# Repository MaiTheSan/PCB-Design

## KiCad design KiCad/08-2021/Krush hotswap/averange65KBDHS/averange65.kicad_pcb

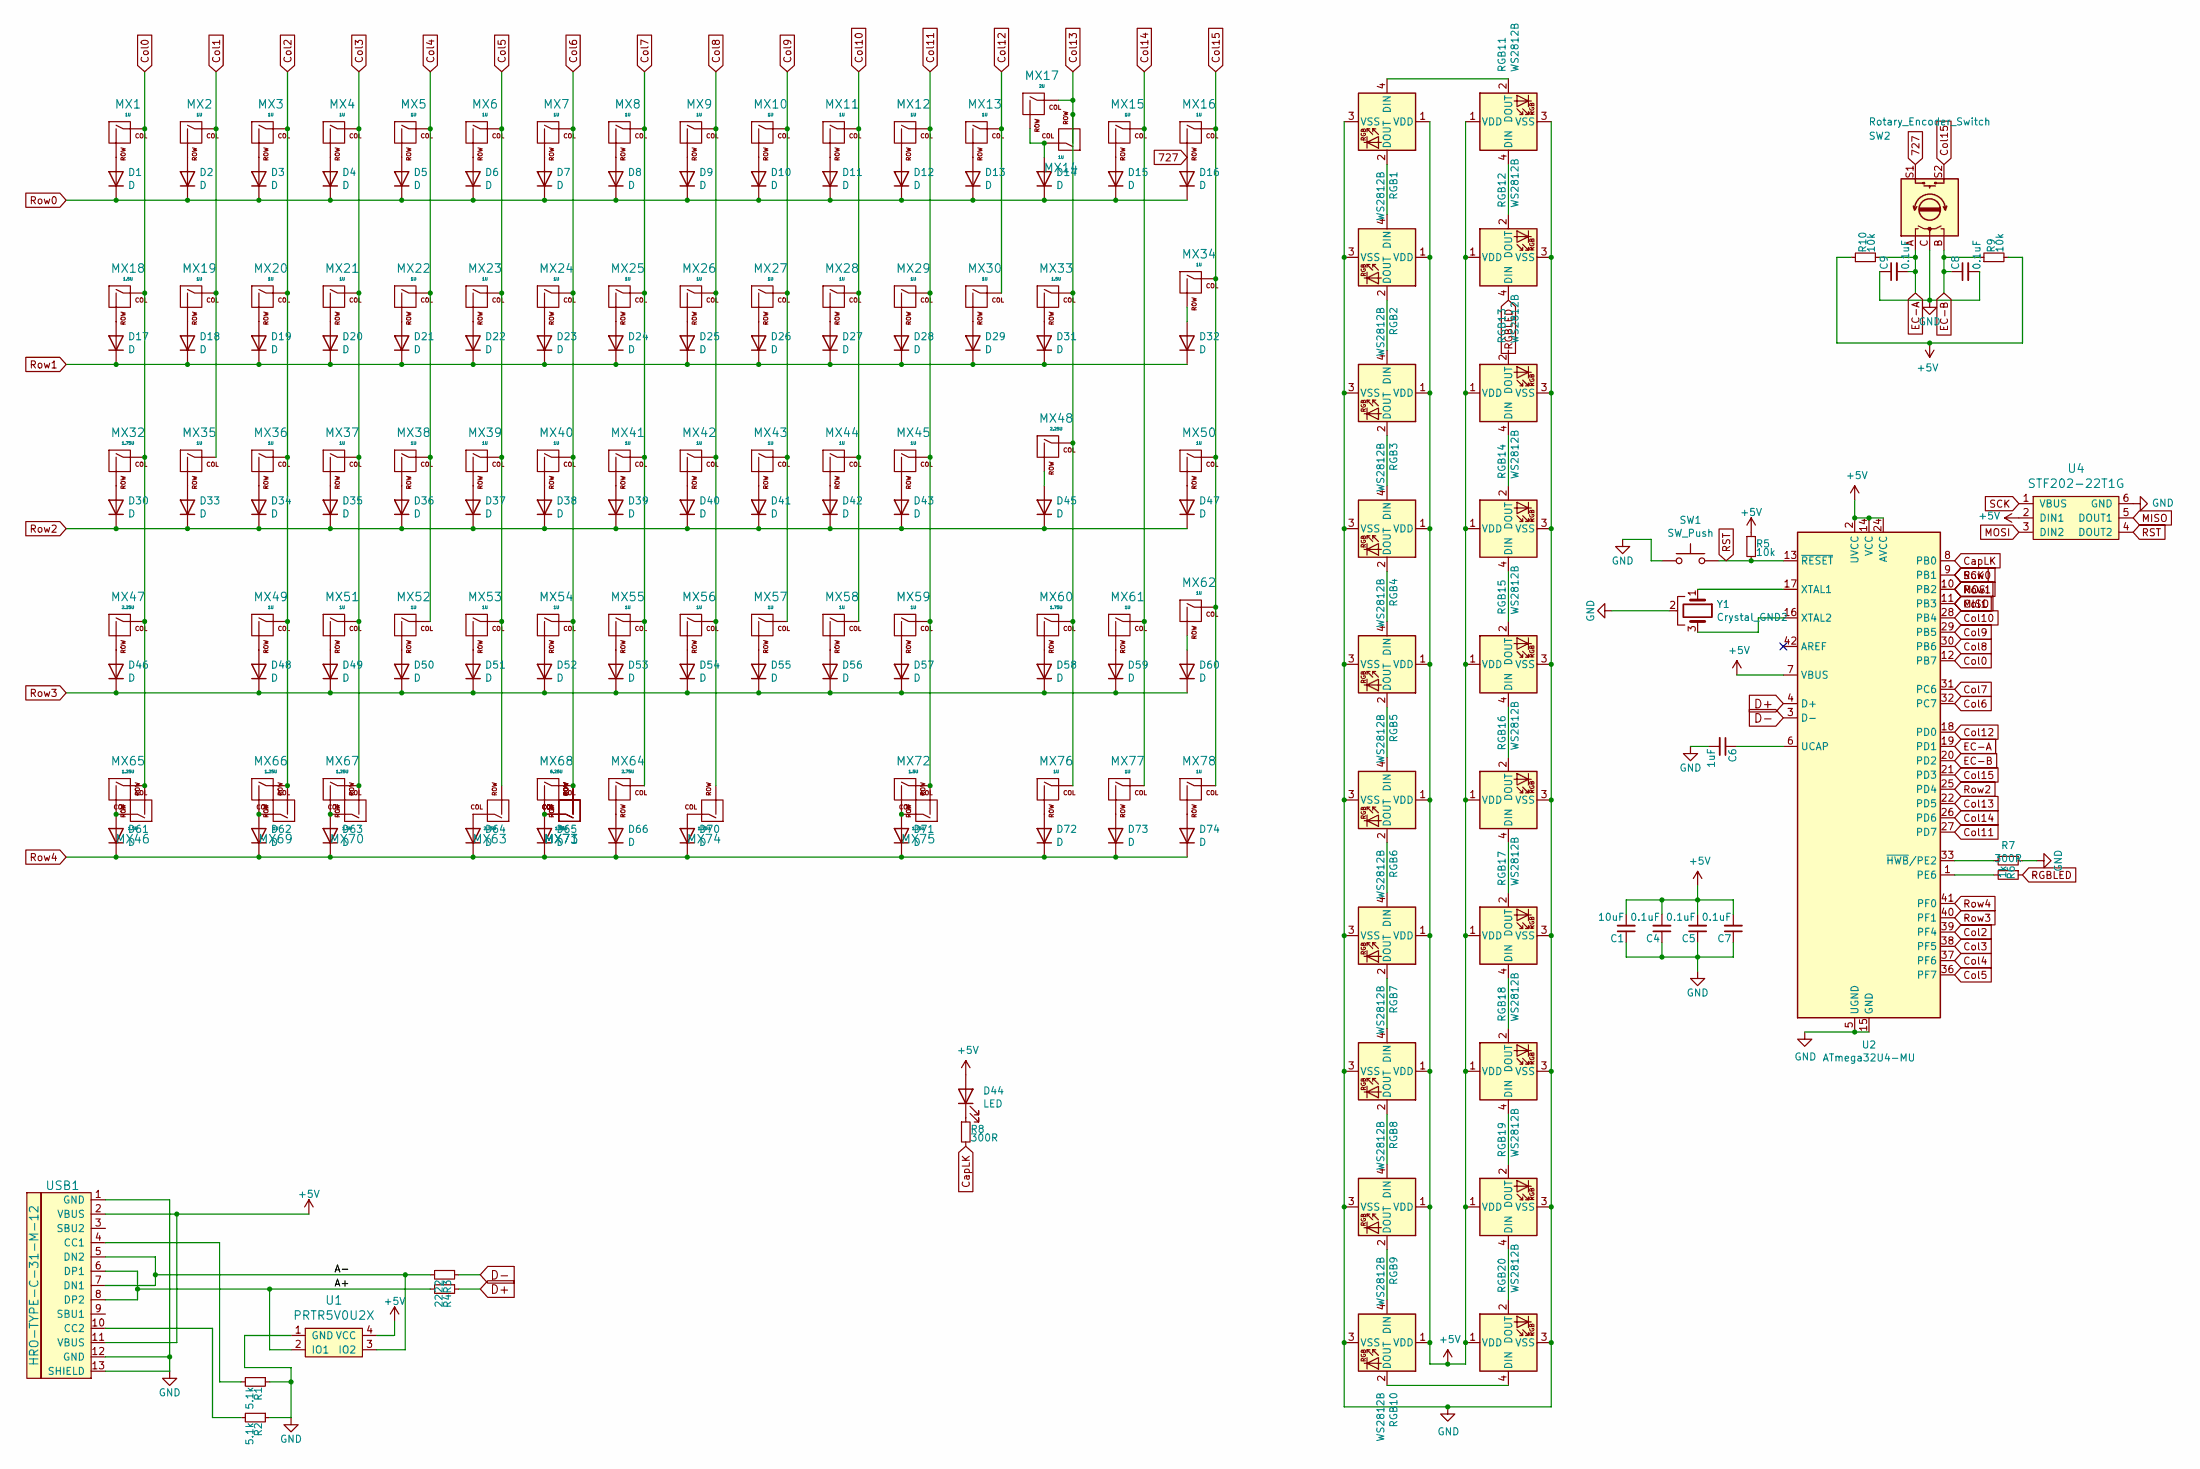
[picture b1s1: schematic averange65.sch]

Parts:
C1: 10uF; C_0603
C4, C5, C7, C8, C9: 0.1uF; C_0603
C6: 1uF; C_0603
D1, D2, D3, D4, D5, D6, D7, D8, D9, D10, D11, D12, D13, D14, D15, D16, D17, D18, D19, D20, D21, D22, D23, D24, D25, D26, D27, D28, D29, D30, D31, D32, D33, D34, D35, D36, D37, D38, D39, D40, D41, D42, D43, D45, D46, D47, D48, D49, D50, D51, D52, D53, D54, D55, D56, D57, D58, D59, D60, D61, D62, D63, D64, D65, D66, D70, D71, D72, D73, D74: D; DIODE_1206_SawnsProjects
D44: LED; LED-6028
MX1, MX2, MX3, MX4, MX5, MX6, MX7, MX8, MX9, MX10, MX11, MX12, MX13, MX14, MX15, MX16, MX19, MX20, MX21, MX22, MX23, MX24, MX25, MX26, MX27, MX28, MX29, MX30, MX34, MX35, MX36, MX37, MX38, MX39, MX40, MX41, MX42, MX43, MX44, MX45, MX49, MX50, MX51, MX52, MX53, MX54, MX55, MX56, MX57, MX58, MX59, MX61, MX62, MX69, MX76, MX77, MX78: 1U; MXOnly-1U-Hotswap
MX17: 2U; MXOnly-2U-Hotswap
MX18, MX33, MX46, MX70, MX72: 1.5U; MXOnly-1.5U-Hotswap
MX32, MX60: 1.75U; MXOnly-1.75U-Hotswap
MX47, MX48: 2.25U; MXOnly-2.25U-Hotswap
MX63: 2.25U; MXOnly-2.25U-Hotswap-ReversedStabilizers
MX64: 2.75U; MXOnly-2.75U-Hotswap-ReversedStabilizers
MX65, MX66, MX67, MX73, MX74, MX75: 1.25U; MXOnly-1.25U-Hotswap
MX68: 6.25U; MXOnly-6.25U-Hotswap
MX71: 7U; MXOnly-7U-Hotswap-ReversedStabilizers
R1, R2: 5.1k; R_0805
R3, R4: 22; R_0603
R5, R9, R10: 10k; R_0805
R6: 1k; R_0805
R7, R8: 300R; R_0805
RGB1, RGB2, RGB3, RGB4, RGB5, RGB6, RGB7, RGB8, RGB9, RGB10, RGB11, RGB12, RGB13, RGB14, RGB15, RGB16, RGB17, RGB18, RGB19, RGB20: WS2812B; LED_WS2812B_PLCC4_5.0x5.0mm_P3.2mm
SW1: SW_Push; SKQG-1155865
SW2: Rotary_Encoder_Switch; RotaryEncoder_Alps_EC11E-Switch_Vertical_H20mm_Center
U1: PRTR5V0U2X; SOT143B
U2: ATmega32U4-MU; QFN-44-1EP_7x7mm_P0.5mm_EP5.15x5.15mm
U4: STF202-22T1G; Tag-Connect_TC2030-IDC-NL_2x03_P1.27mm_Vertical
USB1: HRO-TYPE-C-31-M-12; HRO-TYPE-C-31-M-12-Assembly
Y1: Crystal_GND2; Resonator_SMD_muRata_CSTxExxV-3Pin_3.0x1.1mm

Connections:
727: D16.2 (A), MX16.2 (ROW), SW2.S1
+5V: C1.2, C4.2, C5.2, C7.2, D44.2 (A), R5.1, R9.2, R10.1, RGB1.1 (VDD), RGB2.1 (VDD), RGB3.1 (VDD), RGB4.1 (VDD), RGB5.1 (VDD), RGB6.1 (VDD), RGB7.1 (VDD), RGB8.1 (VDD), RGB9.1 (VDD), RGB10.1 (VDD), RGB11.1 (VDD), RGB12.1 (VDD), RGB13.1 (VDD), RGB14.1 (VDD), RGB15.1 (VDD), RGB16.1 (VDD), RGB17.1 (VDD), RGB18.1 (VDD), RGB19.1 (VDD), RGB20.1 (VDD), U1.4 (VCC), U2.2 (UVCC), U2.7 (VBUS), U2.14 (VCC), U2.24 (AVCC), U2.34 (VCC), U2.44 (AVCC), U4.2 (DIN1), USB1.2 (VBUS), USB1.11 (VBUS)
/A+: R4.2, U1.2 (IO1), USB1.6 (DP1), USB1.8 (DP2)
/A-: R3.2, U1.3 (IO2), USB1.5 (DN2), USB1.7 (DN1)
CapLK: R8.2, U2.8 (PB0)
Col0: MX1.1 (COL), MX18.1 (COL), MX32.1 (COL), MX46.2 (ROW), MX47.1 (COL), MX65.1 (COL), U2.12 (PB7)
Col1: MX2.1 (COL), MX19.1 (COL), MX35.1 (COL), U2.11 (PB3), U4.5 (DOUT1)
Col2: MX3.1 (COL), MX20.1 (COL), MX36.1 (COL), MX49.1 (COL), MX66.1 (COL), MX69.2 (ROW), U2.39 (PF4)
Col3: MX4.1 (COL), MX21.1 (COL), MX37.1 (COL), MX51.1 (COL), MX67.1 (COL), MX70.2 (ROW), U2.38 (PF5)
Col4: MX5.1 (COL), MX22.1 (COL), MX38.1 (COL), MX52.1 (COL), U2.37 (PF6)
Col5: MX6.1 (COL), MX23.1 (COL), MX39.1 (COL), MX53.1 (COL), MX63.2 (ROW), U2.36 (PF7)
Col6: MX7.1 (COL), MX24.1 (COL), MX40.1 (COL), MX54.1 (COL), MX68.1 (COL), MX71.2 (ROW), MX73.2 (ROW), U2.32 (PC7)
Col7: MX8.1 (COL), MX25.1 (COL), MX41.1 (COL), MX55.1 (COL), MX64.1 (COL), U2.31 (PC6)
Col8: MX9.1 (COL), MX26.1 (COL), MX42.1 (COL), MX56.1 (COL), MX74.2 (ROW), U2.30 (PB6)
Col9: MX10.1 (COL), MX27.1 (COL), MX43.1 (COL), MX57.1 (COL), U2.29 (PB5)
Col10: MX11.1 (COL), MX28.1 (COL), MX44.1 (COL), MX58.1 (COL), U2.28 (PB4)
Col11: MX12.1 (COL), MX29.1 (COL), MX45.1 (COL), MX59.1 (COL), MX72.1 (COL), MX75.2 (ROW), U2.27 (PD7)
Col12: MX13.1 (COL), MX30.1 (COL), U2.18 (PD0)
Col13: MX14.2 (ROW), MX17.1 (COL), MX33.1 (COL), MX48.1 (COL), MX60.1 (COL), MX76.1 (COL), U2.22 (PD5)
Col14: MX15.1 (COL), MX61.1 (COL), MX77.1 (COL), U2.26 (PD6)
Col15: MX16.1 (COL), MX34.1 (COL), MX50.1 (COL), MX62.1 (COL), MX78.1 (COL), SW2.S2, U2.21 (PD3)
D+: R4.1, U2.4 (D+)
D-: R3.1, U2.3 (D-)
EC-A: C9.2, R10.2, SW2.A, U2.19 (PD1)
EC-B: C8.1, R9.1, SW2.B, U2.20 (PD2)
GND: C1.1, C4.1, C5.1, C6.2, C7.1, C8.2, C9.1, R1.1, R2.1, R6.1, RGB1.3 (VSS), RGB2.3 (VSS), RGB3.3 (VSS), RGB4.3 (VSS), RGB5.3 (VSS), RGB6.3 (VSS), RGB7.3 (VSS), RGB8.3 (VSS), RGB9.3 (VSS), RGB10.3 (VSS), RGB11.3 (VSS), RGB12.3 (VSS), RGB13.3 (VSS), RGB14.3 (VSS), RGB15.3 (VSS), RGB16.3 (VSS), RGB17.3 (VSS), RGB18.3 (VSS), RGB19.3 (VSS), RGB20.3 (VSS), SW1.1, SW2.C, U1.1 (GND), U2.5 (UGND), U2.15 (GND), U2.23 (GND), U2.35 (GND), U2.43 (GND), U2.45 (GND), U4.6 (GND), USB1.1 (GND), USB1.12 (GND), USB1.13 (SHIELD), Y1.2
MOSI: D17.1 (K), D18.1 (K), D19.1 (K), D20.1 (K), D21.1 (K), D22.1 (K), D23.1 (K), D24.1 (K), D25.1 (K), D26.1 (K), D27.1 (K), D28.1 (K), D29.1 (K), D31.1 (K), D32.1 (K), U2.10 (PB2), U4.3 (DIN2)
unnamed: C6.1, U2.6 (UCAP)
unnamed: D1.2 (A), MX1.2 (ROW)
unnamed: D2.2 (A), MX2.2 (ROW)
unnamed: D3.2 (A), MX3.2 (ROW)
unnamed: D4.2 (A), MX4.2 (ROW)
unnamed: D5.2 (A), MX5.2 (ROW)
unnamed: D6.2 (A), MX6.2 (ROW)
unnamed: D7.2 (A), MX7.2 (ROW)
unnamed: D8.2 (A), MX8.2 (ROW)
unnamed: D9.2 (A), MX9.2 (ROW)
unnamed: D10.2 (A), MX10.2 (ROW)
unnamed: D11.2 (A), MX11.2 (ROW)
unnamed: D12.2 (A), MX12.2 (ROW)
unnamed: D13.2 (A), MX13.2 (ROW)
unnamed: D14.2 (A), MX14.1 (COL), MX17.2 (ROW)
unnamed: D15.2 (A), MX15.2 (ROW)
unnamed: D17.2 (A), MX18.2 (ROW)
unnamed: D18.2 (A), MX19.2 (ROW)
unnamed: D19.2 (A), MX20.2 (ROW)
unnamed: D20.2 (A), MX21.2 (ROW)
unnamed: D21.2 (A), MX22.2 (ROW)
unnamed: D22.2 (A), MX23.2 (ROW)
unnamed: D23.2 (A), MX24.2 (ROW)
unnamed: D24.2 (A), MX25.2 (ROW)
unnamed: D25.2 (A), MX26.2 (ROW)
unnamed: D26.2 (A), MX27.2 (ROW)
unnamed: D27.2 (A), MX28.2 (ROW)
unnamed: D28.2 (A), MX29.2 (ROW)
unnamed: D29.2 (A), MX30.2 (ROW)
unnamed: D30.2 (A), MX32.2 (ROW)
unnamed: D31.2 (A), MX33.2 (ROW)
unnamed: D32.2 (A), MX34.2 (ROW)
unnamed: D33.2 (A), MX35.2 (ROW)
unnamed: D34.2 (A), MX36.2 (ROW)
unnamed: D35.2 (A), MX37.2 (ROW)
unnamed: D36.2 (A), MX38.2 (ROW)
unnamed: D37.2 (A), MX39.2 (ROW)
unnamed: D38.2 (A), MX40.2 (ROW)
unnamed: D39.2 (A), MX41.2 (ROW)
unnamed: D40.2 (A), MX42.2 (ROW)
unnamed: D41.2 (A), MX43.2 (ROW)
unnamed: D42.2 (A), MX44.2 (ROW)
unnamed: D43.2 (A), MX45.2 (ROW)
unnamed: D44.1 (K), R8.1
unnamed: D45.2 (A), MX48.2 (ROW)
unnamed: D46.2 (A), MX47.2 (ROW)
unnamed: D47.2 (A), MX50.2 (ROW)
unnamed: D48.2 (A), MX49.2 (ROW)
unnamed: D49.2 (A), MX51.2 (ROW)
unnamed: D50.2 (A), MX52.2 (ROW)
unnamed: D51.2 (A), MX53.2 (ROW)
unnamed: D52.2 (A), MX54.2 (ROW)
unnamed: D53.2 (A), MX55.2 (ROW)
unnamed: D54.2 (A), MX56.2 (ROW)
unnamed: D55.2 (A), MX57.2 (ROW)
unnamed: D56.2 (A), MX58.2 (ROW)
unnamed: D57.2 (A), MX59.2 (ROW)
unnamed: D58.2 (A), MX60.2 (ROW)
unnamed: D59.2 (A), MX61.2 (ROW)
unnamed: D60.2 (A), MX62.2 (ROW)
unnamed: D61.2 (A), MX46.1 (COL), MX65.2 (ROW)
unnamed: D62.2 (A), MX66.2 (ROW), MX69.1 (COL)
unnamed: D63.2 (A), MX67.2 (ROW), MX70.1 (COL)
unnamed: D64.2 (A), MX63.1 (COL)
unnamed: D65.2 (A), MX68.2 (ROW), MX71.1 (COL), MX73.1 (COL)
unnamed: D66.2 (A), MX64.2 (ROW)
unnamed: D70.2 (A), MX74.1 (COL)
unnamed: D71.2 (A), MX72.2 (ROW), MX75.1 (COL)
unnamed: D72.2 (A), MX76.2 (ROW)
unnamed: D73.2 (A), MX77.2 (ROW)
unnamed: D74.2 (A), MX78.2 (ROW)
unnamed: R1.2, USB1.4 (CC1)
unnamed: R2.2, USB1.10 (CC2)
unnamed: R6.2, U2.33 (~HWB~/PE2)
unnamed: R7.2, U2.1 (PE6)
unnamed: RGB1.2 (DOUT), RGB2.4 (DIN)
unnamed: RGB1.4 (DIN), RGB11.2 (DOUT)
unnamed: RGB2.2 (DOUT), RGB3.4 (DIN)
unnamed: RGB3.2 (DOUT), RGB4.4 (DIN)
unnamed: RGB4.2 (DOUT), RGB5.4 (DIN)
unnamed: RGB5.2 (DOUT), RGB6.4 (DIN)
unnamed: RGB6.2 (DOUT), RGB7.4 (DIN)
unnamed: RGB7.2 (DOUT), RGB8.4 (DIN)
unnamed: RGB8.2 (DOUT), RGB9.4 (DIN)
unnamed: RGB10.2 (DOUT), RGB20.4 (DIN)
unnamed: RGB9.2 (DOUT), RGB10.4 (DIN)
unnamed: RGB11.4 (DIN), RGB12.2 (DOUT)
unnamed: RGB13.4 (DIN), RGB14.2 (DOUT)
unnamed: RGB14.4 (DIN), RGB15.2 (DOUT)
unnamed: RGB15.4 (DIN), RGB16.2 (DOUT)
unnamed: RGB16.4 (DIN), RGB17.2 (DOUT)
unnamed: RGB17.4 (DIN), RGB18.2 (DOUT)
unnamed: RGB18.4 (DIN), RGB19.2 (DOUT)
unnamed: RGB19.4 (DIN), RGB20.2 (DOUT)
unnamed: U2.16 (XTAL2), Y1.3
unnamed: U2.17 (XTAL1), Y1.1
RGBLED: R7.1, RGB12.4 (DIN)
RST: R5.2, SW1.2, U2.13 (~RESET), U4.4 (DOUT2)
Row0: D1.1 (K), D2.1 (K), D3.1 (K), D4.1 (K), D5.1 (K), D6.1 (K), D7.1 (K), D8.1 (K), D9.1 (K), D10.1 (K), D11.1 (K), D12.1 (K), D13.1 (K), D14.1 (K), D15.1 (K), D16.1 (K), U2.9 (PB1), U4.1 (VBUS)
Row2: D30.1 (K), D33.1 (K), D34.1 (K), D35.1 (K), D36.1 (K), D37.1 (K), D38.1 (K), D39.1 (K), D40.1 (K), D41.1 (K), D42.1 (K), D43.1 (K), D45.1 (K), D47.1 (K), U2.25 (PD4)
Row3: D46.1 (K), D48.1 (K), D49.1 (K), D50.1 (K), D51.1 (K), D52.1 (K), D53.1 (K), D54.1 (K), D55.1 (K), D56.1 (K), D57.1 (K), D58.1 (K), D59.1 (K), D60.1 (K), U2.40 (PF1)
Row4: D61.1 (K), D62.1 (K), D63.1 (K), D64.1 (K), D65.1 (K), D66.1 (K), D70.1 (K), D71.1 (K), D72.1 (K), D73.1 (K), D74.1 (K), U2.41 (PF0)

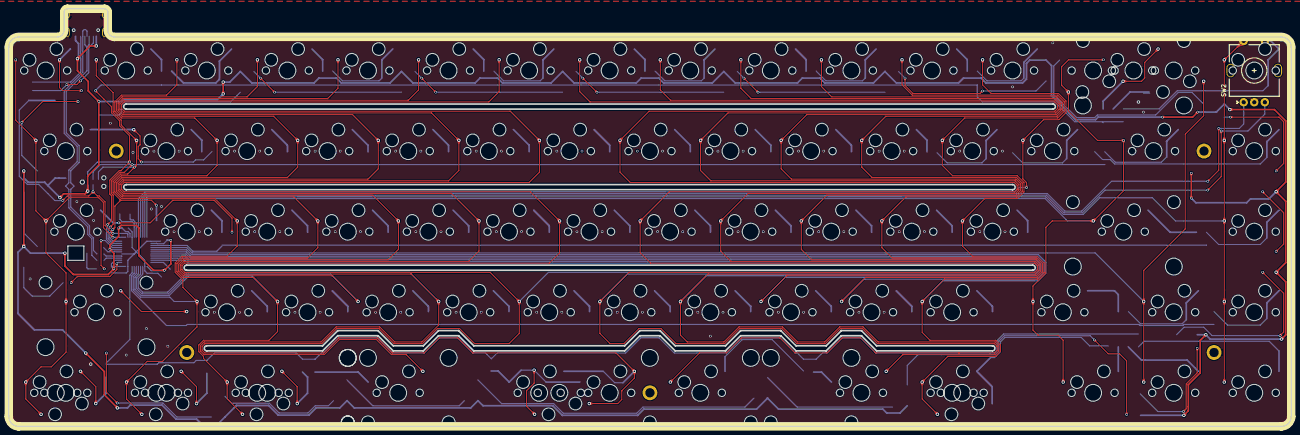
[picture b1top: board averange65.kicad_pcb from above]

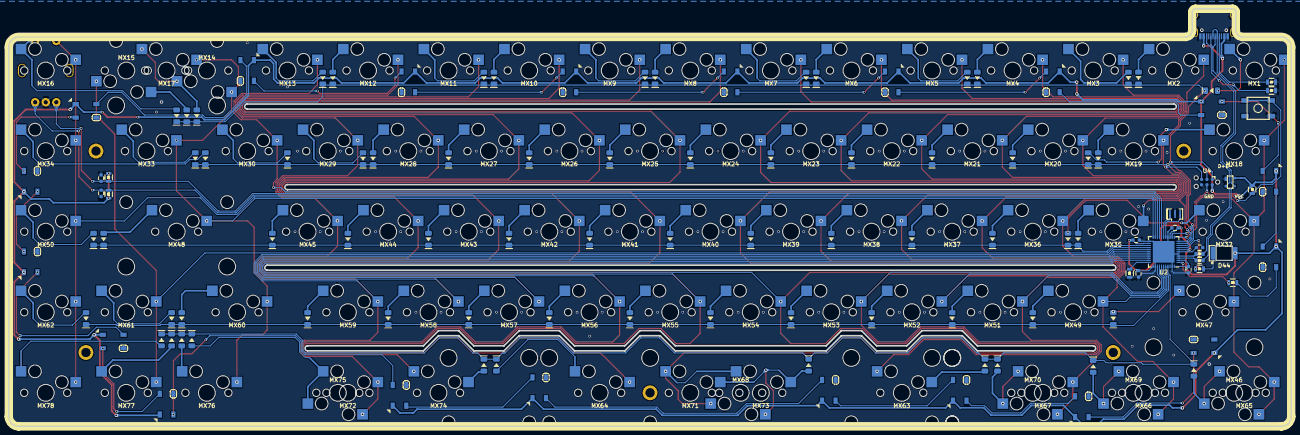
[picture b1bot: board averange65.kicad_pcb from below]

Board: 2 copper layers, 303.2 x 98.7 mm, 197 parts (114 on the bottom side), 129 nets.

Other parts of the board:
H1, H2, H3, H4, H7: MountingHole; MountingHole_2.2mm_M2_ISO7380_Pad

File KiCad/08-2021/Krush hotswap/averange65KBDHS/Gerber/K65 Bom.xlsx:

Tự cung cấp | Diode 1206 | Diode | D1 | D2 | D3 | D4 | D5 | D6 | D7 | D8 | D9 | D10 | D11 | D12 | D13 | D14 | D15 | D16 | D17 | D18 | D19 | D20 | D21 | D22 | D23 | D24 | D25 | D26 | D27 | D28 | D29 | D30 | D31 | D32 | D33 | D34 | D35 | D36 | D37 | D38 | D39 | D40 | D41 | D42 | D43 | D45 | D46 | D47 | D48 | D49 | D50 | D51 | D52 | D53 | D54 | D55 | D56 | D57 | D58 | D59 | D60 | D61 | D62 | D63 | D64 | D65 | D66 | D67 | D68 | D69 | D70 | D71 | D72 | D73 | D74
Tự cung cấp | LED 6028 | LED | D44
Tự cung cấp | Socket hotswap | MX_Switch | MX1 | MX2 | MX3 | MX4 | MX5 | MX6 | MX7 | MX8 | MX9 | MX10 | MX11 | MX12 | MX13 | MX14 | MX15 | MX16 | MX17 | MX18 | MX19 | MX20 | MX21 | MX22 | MX23 | MX24 | MX25 | MX26 | MX27 | MX28 | MX29 | MX30 | MX32 | MX33 | MX34 | MX35 | MX36 | MX37 | MX38 | MX39 | MX40 | MX41 | MX42 | MX43 | MX44 | MX45 | MX46 | MX47 | MX48 | MX49 | MX50 | MX51 | MX52 | MX53 | MX54 | MX55 | MX56 | MX57 | MX58 | MX59 | MX60 | MX61 | MX62 | MX63 | MX64 | MX65 | MX66 | MX67 | MX68 | MX69 | MX70 | MX71 | MX72 | MX73 | MX74 | MX75 | MX76 | MX77 | MX78
Tự cung cấp | LED 5050 | WS2812B | RGB1 | RGB2 | RGB3 | RGB4 | RGB5 | RGB6 | RGB7 | RGB8 | RGB9 | RGB10 | RGB11 | RGB12 | RGB13 | RGB14 | RGB15 | RGB16 | RGB17 | RGB18 | RGB19 | RGB20
x | C0603 | 1uF | C6 |  |  |  |  |  | x1 | 150
x | C0603 | 0.1uF | C4 | C5 | C7 | C8 | C9 |  | x5 | 750
x | C0603 | 10uF | C1 |  |  |  |  |  | x1 | 150
x | R0805 | 5.1k | R1 | R2 |  |  |  |  | x2 | 300
x | R0805 | 1k | R6 |  |  |  |  |  | x1 | 150
x | R0805 | 300R | R7 | R8 |  |  |  |  | x2 | 300
x | R0805 | 10k | R5 | R9 | R10 |  |  |  | x3 | 450
x | R0603 | 22R | R3 | R4 |  |  |  |  | x2 | 300
x | PRTR | PRTR5V0U2 | U1
x | USB | HRO-31M12 | USB1
x | Crystal | CSTCE16M0V53-R0 | Y1
x | MCU | Atmega32U4 | U2
x | Button |  | SW1

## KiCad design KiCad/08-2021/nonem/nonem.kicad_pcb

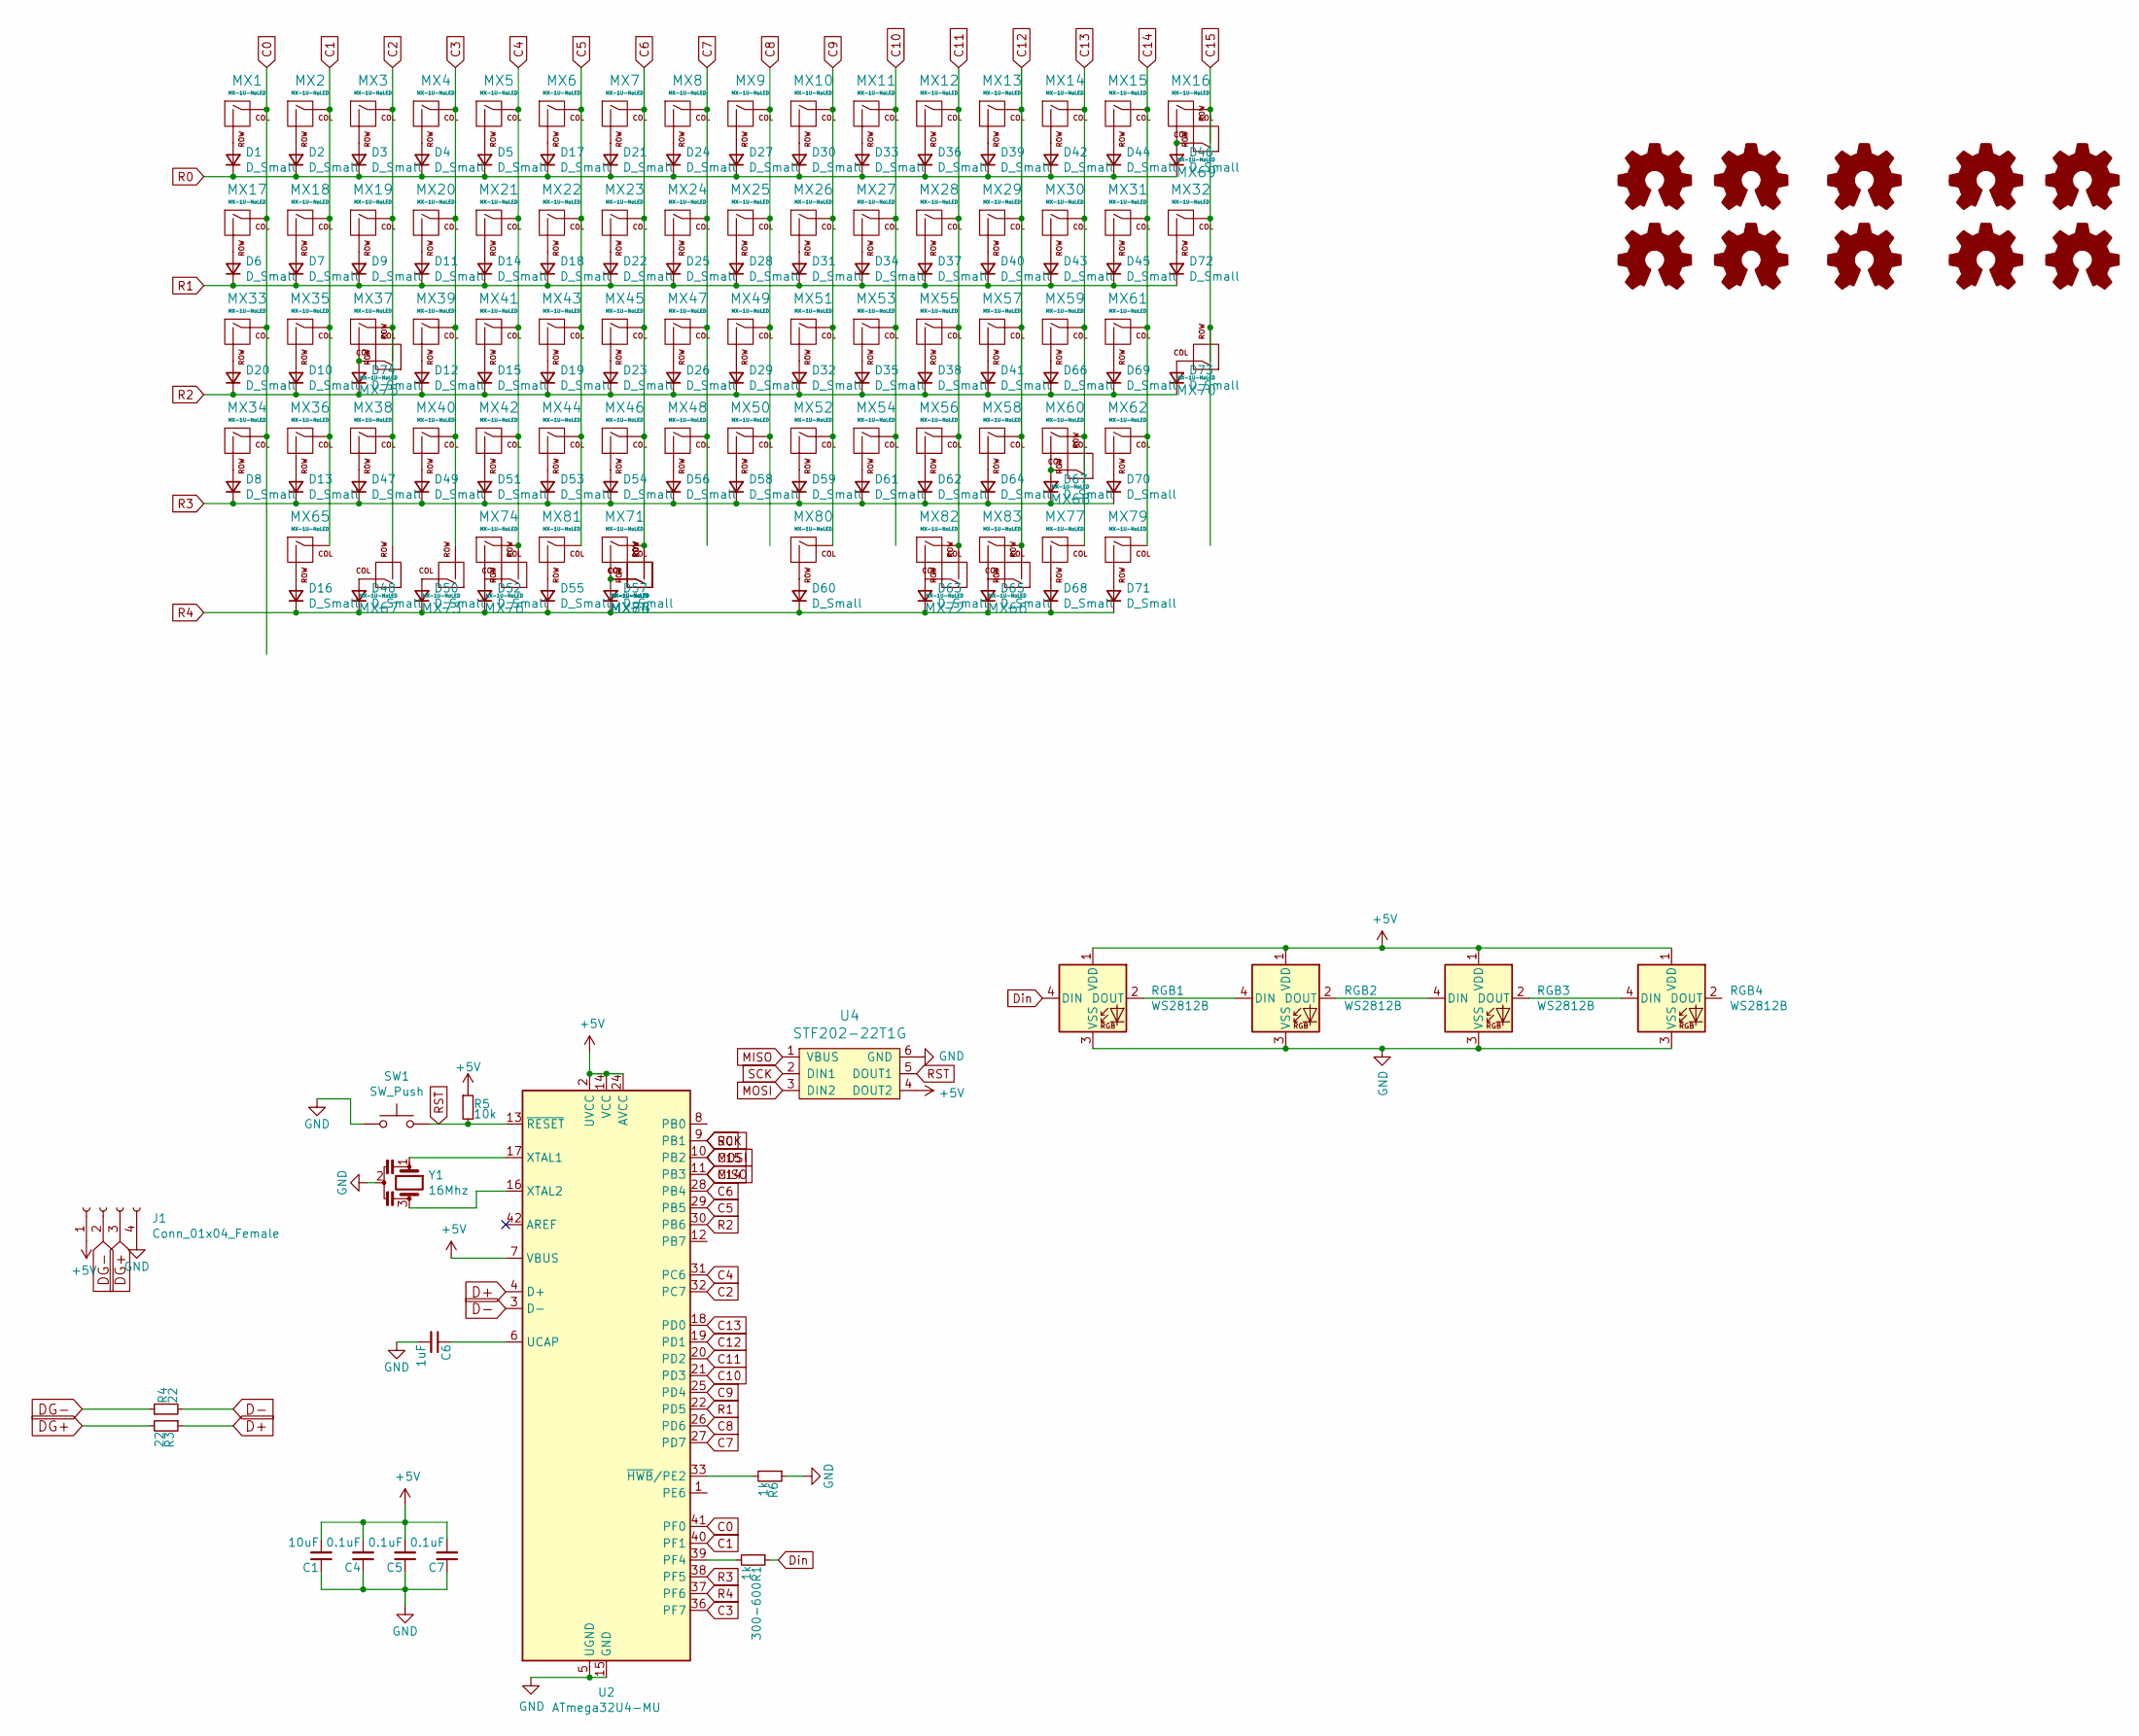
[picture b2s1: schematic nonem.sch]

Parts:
300-600R1: 1k; R_0805
C1: 10uF; C_0603
C4, C5, C7: 0.1uF; C_0603
C6: 1uF; C_0603
D1, D2, D3, D4, D5, D6, D7, D8, D9, D10, D11, D12, D13, D14, D15, D16, D17, D18, D19, D20, D21, D22, D23, D24, D25, D26, D27, D28, D29, D30, D31, D32, D33, D34, D35, D36, D37, D38, D39, D40, D41, D42, D43, D44, D45, D46, D47, D48, D49, D50, D51, D52, D53, D54, D55, D56, D57, D58, D59, D60, D61, D62, D63, D64, D65, D66, D67, D68, D69, D70, D71, D72, D73, D74: D_Small; D_SOD-123
J1: Conn_01x04_Female; JST-SR-4
LOGO1, LOGO2, LOGO3, LOGO4, LOGO5, LOGO6, LOGO7, LOGO8, LOGO9, LOGO10: Logo_Open_Hardware_Small; MountingHole_2.2mm_M2_ISO14580_Pad
MX1, MX2, MX3, MX4, MX5, MX6, MX7, MX8, MX9, MX10, MX11, MX12, MX13, MX14, MX15, MX17, MX18, MX20, MX21, MX22, MX23, MX24, MX25, MX26, MX27, MX28, MX29, MX30, MX31, MX33, MX34, MX35, MX36, MX39, MX40, MX41, MX42, MX43, MX44, MX45, MX46, MX47, MX48, MX49, MX50, MX51, MX52, MX53, MX54, MX55, MX56, MX57, MX58, MX59, MX62, MX65, MX67, MX69, MX70, MX81, MX82: MX-1U-NoLED; MXOnly-1U-Hotswap
MX16: MX-1U-NoLED; MXOnly-2U-Hotswap
MX19, MX32, MX76, MX79, MX83: MX-1U-NoLED; MXOnly-1.5U-Hotswap
MX37, MX60: MX-1U-NoLED; MXOnly-1.75U-Hotswap
MX38, MX61: MX-1U-NoLED; MXOnly-2.25U-Hotswap
MX66, MX72, MX73, MX74, MX75, MX77: MX-1U-NoLED; MXOnly-1.25U-Hotswap
MX68, MX78: MX-1U-NoLED; MXOnly-2.75U-Hotswap
MX71: MX-1U-NoLED; MXOnly-6.25U-Hotswap-ReversedStabilizers
MX80: MX-1U-NoLED; MXOnly-2.25U-Hotswap-ReversedStabilizers
MX84: MX-1U-NoLED; MXOnly-7U-Hotswap
R3, R4: 22; R_0805
R5: 10k; R_0805
R6: 1k; R_0805
RGB1, RGB2, RGB3, RGB4: WS2812B; RGB-6028-mid
SW1: SW_Push; SKQG-1155865
U2: ATmega32U4-MU; QFN-44-1EP_7x7mm_P0.5mm_EP5.15x5.15mm
U4: STF202-22T1G; Reset_Pretty
Y1: 16Mhz; Resonator_SMD_muRata_CSTxExxV-3Pin_3.0x1.1mm

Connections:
+5V: C1.2, C4.2, C5.2, C7.2, J1.1, R5.1, RGB1.1 (VDD), RGB2.1 (VDD), RGB3.1 (VDD), RGB4.1 (VDD), U2.2 (UVCC), U2.7 (VBUS), U2.14 (VCC), U2.24 (AVCC), U2.34 (VCC), U2.44 (AVCC), U4.4 (DOUT2)
C0: MX1.1 (COL), MX17.1 (COL), MX33.1 (COL), MX34.1 (COL), U2.41 (PF0)
C1: MX2.1 (COL), MX18.1 (COL), MX35.1 (COL), MX36.1 (COL), MX65.1 (COL), U2.40 (PF1)
C2: MX3.1 (COL), MX19.1 (COL), MX37.1 (COL), MX38.1 (COL), MX67.2 (ROW), MX75.2 (ROW), U2.32 (PC7)
C3: MX4.1 (COL), MX20.1 (COL), MX39.1 (COL), MX40.1 (COL), MX73.2 (ROW), U2.36 (PF7)
C4: MX5.1 (COL), MX21.1 (COL), MX41.1 (COL), MX42.1 (COL), MX74.1 (COL), MX76.2 (ROW), U2.31 (PC6)
C5: MX6.1 (COL), MX22.1 (COL), MX43.1 (COL), MX44.1 (COL), MX81.1 (COL), U2.29 (PB5)
C6: MX7.1 (COL), MX23.1 (COL), MX45.1 (COL), MX46.1 (COL), MX71.1 (COL), MX78.2 (ROW), MX84.2 (ROW), U2.28 (PB4)
C7: MX8.1 (COL), MX24.1 (COL), MX47.1 (COL), MX48.1 (COL), U2.27 (PD7)
C8: MX9.1 (COL), MX25.1 (COL), MX49.1 (COL), MX50.1 (COL), U2.26 (PD6)
C9: MX10.1 (COL), MX26.1 (COL), MX51.1 (COL), MX52.1 (COL), MX80.1 (COL), U2.25 (PD4)
C10: MX11.1 (COL), MX27.1 (COL), MX53.1 (COL), MX54.1 (COL), U2.21 (PD3)
C11: MX12.1 (COL), MX28.1 (COL), MX55.1 (COL), MX56.1 (COL), MX72.2 (ROW), MX82.1 (COL), U2.20 (PD2)
C12: MX13.1 (COL), MX29.1 (COL), MX57.1 (COL), MX58.1 (COL), MX66.2 (ROW), MX83.1 (COL), U2.19 (PD1)
C13: MX14.1 (COL), MX30.1 (COL), MX59.1 (COL), MX60.1 (COL), MX68.2 (ROW), MX77.1 (COL), U2.18 (PD0)
C14: MX15.1 (COL), MX31.1 (COL), MX61.1 (COL), MX62.1 (COL), MX79.1 (COL), U2.11 (PB3), U4.1 (VBUS)
C15: MX16.1 (COL), MX32.1 (COL), MX69.2 (ROW), MX70.2 (ROW), U2.10 (PB2), U4.3 (DIN2)
D+: R3.1, U2.4 (D+)
D-: R4.2, U2.3 (D-)
DG+: J1.3, R3.2
DG-: J1.2, R4.1
Din: 300-600R1.1, RGB1.4 (DIN)
GND: C1.1, C4.1, C5.1, C6.2, C7.1, J1.4, R6.1, RGB1.3 (VSS), RGB2.3 (VSS), RGB3.3 (VSS), RGB4.3 (VSS), SW1.1, U2.5 (UGND), U2.15 (GND), U2.23 (GND), U2.35 (GND), U2.43 (GND), U2.45 (GND), U4.6 (GND), Y1.2
unnamed: 300-600R1.2, U2.39 (PF4)
unnamed: C6.1, U2.6 (UCAP)
unnamed: D1.2 (A), MX1.2 (ROW)
unnamed: D2.2 (A), MX2.2 (ROW)
unnamed: D3.2 (A), MX3.2 (ROW)
unnamed: D4.2 (A), MX4.2 (ROW)
unnamed: D5.2 (A), MX5.2 (ROW)
unnamed: D6.2 (A), MX17.2 (ROW)
unnamed: D7.2 (A), MX18.2 (ROW)
unnamed: D8.2 (A), MX34.2 (ROW)
unnamed: D9.2 (A), MX19.2 (ROW)
unnamed: D10.2 (A), MX35.2 (ROW)
unnamed: D11.2 (A), MX20.2 (ROW)
unnamed: D12.2 (A), MX39.2 (ROW)
unnamed: D13.2 (A), MX36.2 (ROW)
unnamed: D14.2 (A), MX21.2 (ROW)
unnamed: D15.2 (A), MX41.2 (ROW)
unnamed: D16.2 (A), MX65.2 (ROW)
unnamed: D17.2 (A), MX6.2 (ROW)
unnamed: D18.2 (A), MX22.2 (ROW)
unnamed: D19.2 (A), MX43.2 (ROW)
unnamed: D20.2 (A), MX33.2 (ROW)
unnamed: D21.2 (A), MX7.2 (ROW)
unnamed: D22.2 (A), MX23.2 (ROW)
unnamed: D23.2 (A), MX45.2 (ROW)
unnamed: D24.2 (A), MX8.2 (ROW)
unnamed: D25.2 (A), MX24.2 (ROW)
unnamed: D26.2 (A), MX47.2 (ROW)
unnamed: D27.2 (A), MX9.2 (ROW)
unnamed: D28.2 (A), MX25.2 (ROW)
unnamed: D29.2 (A), MX49.2 (ROW)
unnamed: D30.2 (A), MX10.2 (ROW)
unnamed: D31.2 (A), MX26.2 (ROW)
unnamed: D32.2 (A), MX51.2 (ROW)
unnamed: D33.2 (A), MX11.2 (ROW)
unnamed: D34.2 (A), MX27.2 (ROW)
unnamed: D35.2 (A), MX53.2 (ROW)
unnamed: D36.2 (A), MX12.2 (ROW)
unnamed: D37.2 (A), MX28.2 (ROW)
unnamed: D38.2 (A), MX55.2 (ROW)
unnamed: D39.2 (A), MX13.2 (ROW)
unnamed: D40.2 (A), MX29.2 (ROW)
unnamed: D41.2 (A), MX57.2 (ROW)
unnamed: D42.2 (A), MX14.2 (ROW)
unnamed: D43.2 (A), MX30.2 (ROW)
unnamed: D44.2 (A), MX15.2 (ROW)
unnamed: D45.2 (A), MX31.2 (ROW)
unnamed: D46.2 (A), MX16.2 (ROW), MX69.1 (COL)
unnamed: D47.2 (A), MX38.2 (ROW)
unnamed: D48.2 (A), MX67.1 (COL)
unnamed: D49.2 (A), MX40.2 (ROW)
unnamed: D50.2 (A), MX73.1 (COL)
unnamed: D51.2 (A), MX42.2 (ROW)
unnamed: D52.2 (A), MX74.2 (ROW), MX76.1 (COL)
unnamed: D53.2 (A), MX44.2 (ROW)
unnamed: D54.2 (A), MX46.2 (ROW)
unnamed: D55.2 (A), MX81.2 (ROW)
unnamed: D56.2 (A), MX48.2 (ROW)
unnamed: D57.2 (A), MX71.2 (ROW), MX78.1 (COL), MX84.1 (COL)
unnamed: D58.2 (A), MX50.2 (ROW)
unnamed: D59.2 (A), MX52.2 (ROW)
unnamed: D60.2 (A), MX80.2 (ROW)
unnamed: D61.2 (A), MX54.2 (ROW)
unnamed: D62.2 (A), MX56.2 (ROW)
unnamed: D63.2 (A), MX72.1 (COL), MX82.2 (ROW)
unnamed: D64.2 (A), MX58.2 (ROW)
unnamed: D65.2 (A), MX66.1 (COL), MX83.2 (ROW)
unnamed: D66.2 (A), MX59.2 (ROW)
unnamed: D67.2 (A), MX60.2 (ROW), MX68.1 (COL)
unnamed: D68.2 (A), MX77.2 (ROW)
unnamed: D69.2 (A), MX61.2 (ROW)
unnamed: D70.2 (A), MX62.2 (ROW)
unnamed: D71.2 (A), MX79.2 (ROW)
unnamed: D72.2 (A), MX32.2 (ROW)
unnamed: D73.2 (A), MX70.1 (COL)
unnamed: D74.2 (A), MX37.2 (ROW), MX75.1 (COL)
unnamed: R6.2, U2.33 (~HWB~/PE2)
unnamed: RGB1.2 (DOUT), RGB2.4 (DIN)
unnamed: RGB2.2 (DOUT), RGB3.4 (DIN)
unnamed: RGB3.2 (DOUT), RGB4.4 (DIN)
unnamed: U2.16 (XTAL2), Y1.3
unnamed: U2.17 (XTAL1), Y1.1
R0: D1.1 (K), D2.1 (K), D3.1 (K), D4.1 (K), D5.1 (K), D17.1 (K), D21.1 (K), D24.1 (K), D27.1 (K), D30.1 (K), D33.1 (K), D36.1 (K), D39.1 (K), D42.1 (K), D44.1 (K), D46.1 (K), U2.9 (PB1), U4.2 (DIN1)
R1: D6.1 (K), D7.1 (K), D9.1 (K), D11.1 (K), D14.1 (K), D18.1 (K), D22.1 (K), D25.1 (K), D28.1 (K), D31.1 (K), D34.1 (K), D37.1 (K), D40.1 (K), D43.1 (K), D45.1 (K), D72.1 (K), U2.22 (PD5)
R2: D10.1 (K), D12.1 (K), D15.1 (K), D19.1 (K), D20.1 (K), D23.1 (K), D26.1 (K), D29.1 (K), D32.1 (K), D35.1 (K), D38.1 (K), D41.1 (K), D66.1 (K), D69.1 (K), D73.1 (K), D74.1 (K), U2.30 (PB6)
R3: D8.1 (K), D13.1 (K), D47.1 (K), D49.1 (K), D51.1 (K), D53.1 (K), D54.1 (K), D56.1 (K), D58.1 (K), D59.1 (K), D61.1 (K), D62.1 (K), D64.1 (K), D67.1 (K), D70.1 (K), U2.38 (PF5)
R4: D16.1 (K), D48.1 (K), D50.1 (K), D52.1 (K), D55.1 (K), D57.1 (K), D60.1 (K), D63.1 (K), D65.1 (K), D68.1 (K), D71.1 (K), U2.37 (PF6)
RST: R5.2, SW1.2, U2.13 (~RESET), U4.5 (DOUT1)

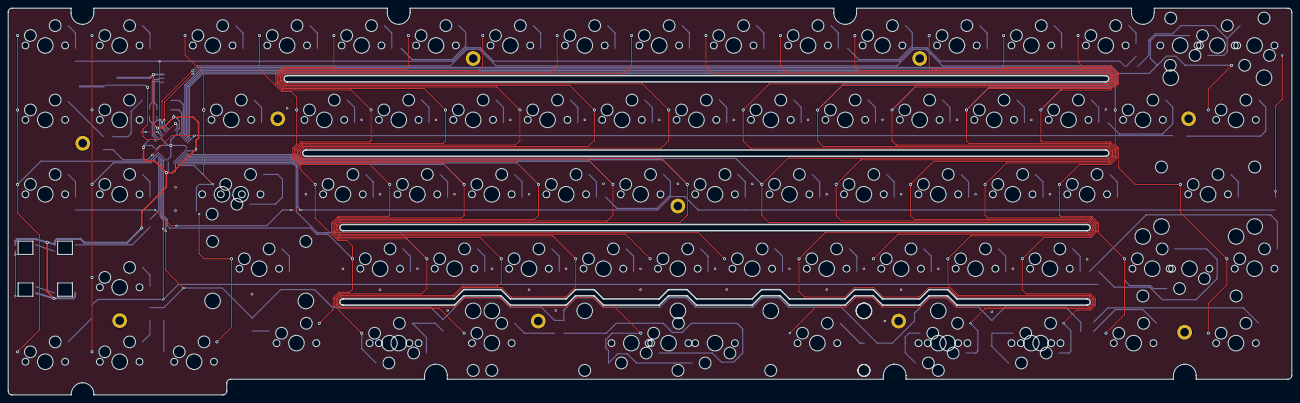
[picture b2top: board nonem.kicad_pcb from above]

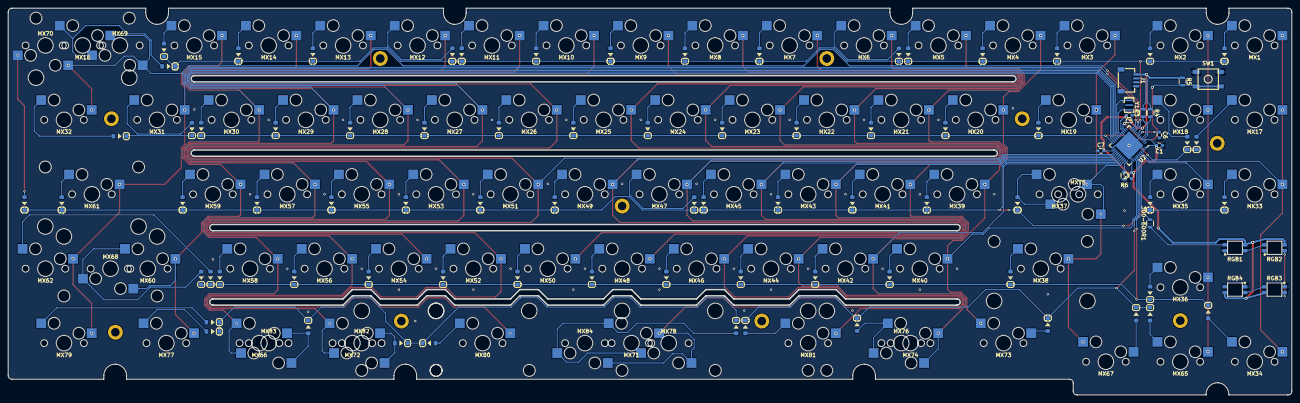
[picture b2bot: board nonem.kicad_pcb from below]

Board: 2 copper layers, 328.6 x 99.0 mm, 184 parts (92 on the bottom side), 111 nets.
